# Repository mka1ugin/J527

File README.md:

# J527
## Дополнительный контроллер для подрулевого блока 5K0953569, реализующий работу кнопки ассистентов, круиза и обогрева руля

Руль от Skoda 2021 5E3419093CVKH оборудован обогревом руля, кнопкой включения и выключения подогрева, а также кнопками быстрого вызова ассистентов и установки скорости круиз-контроля. Руль дооснащён LIN-LIN конвертером https://github.com/mka1ugin/LIN_MFSW_Adapter и установлен на VW Passat B6.
Подрулевой блок 5K0953569T доработан путём установки дополнительных шлейфов обогрева руля от блока 5Q1953569B. 
Контроллер выполнен на МК STM32F103C8T6 и реализует следующие функции:
* Управление работой обогрева руля
* Эмуляция нажатия кнопки быстрого вызова ассистентов
* Эмуляция нажатия кнопки задания скорости круиз-контроля

## Контроль обогрева руля

Сигнал нажатия кнопки обогрева руля отслеживается через LIN-шину. Нажатие кнопки включает и выключает обогрев руля. Питание на обогрев подаётся с клеммы 15 и только при включенном зажигании. Кроме того, контроллер отслеживает напряжение питания и работа возможна только при напряжении выше 12.5 В (настраивается в прошивке), т.е. при работающем двигателе. Силовой ключ VN7010A взят из блока 5Q1953569B.
Контроллер оборудован FRAM-памятью FM24CL16, в которую записывается каждое изменение состояния обогрева. Таким образом, если машина была заглушена со включенным обогревом, при следующем запуске двигателя обогрев будет включен автоматически.

## Эмуляция нажатия кнопок

Контроллер управляет двумя герконовыми реле серии EDR3. Их контактные группы включены параллельно штатным кнопкам "SET" круиз-контроля и кнопке быстрого вызова ассистентов. Контакты геркона дублируют состояние соответствующих кнопок на руле.

## Реализация

Контроллер выполнен на односторонней плате размером 50x47.5 мм и соединяется с блоком подрулевых переключателей двумя разъёмами: трёхконтактный - питание 12В и LIN-шина, и пятиконтактный - эмуляция нажатия кнопок. Также контроллер имеет два силовых четырёхконтактных разъёма - вход силового питания и выход на шлейф обогрева.

## Видео работы:
<p align="center">
  <a href="https://youtu.be/Oqg4uzVC5qI">
</p>

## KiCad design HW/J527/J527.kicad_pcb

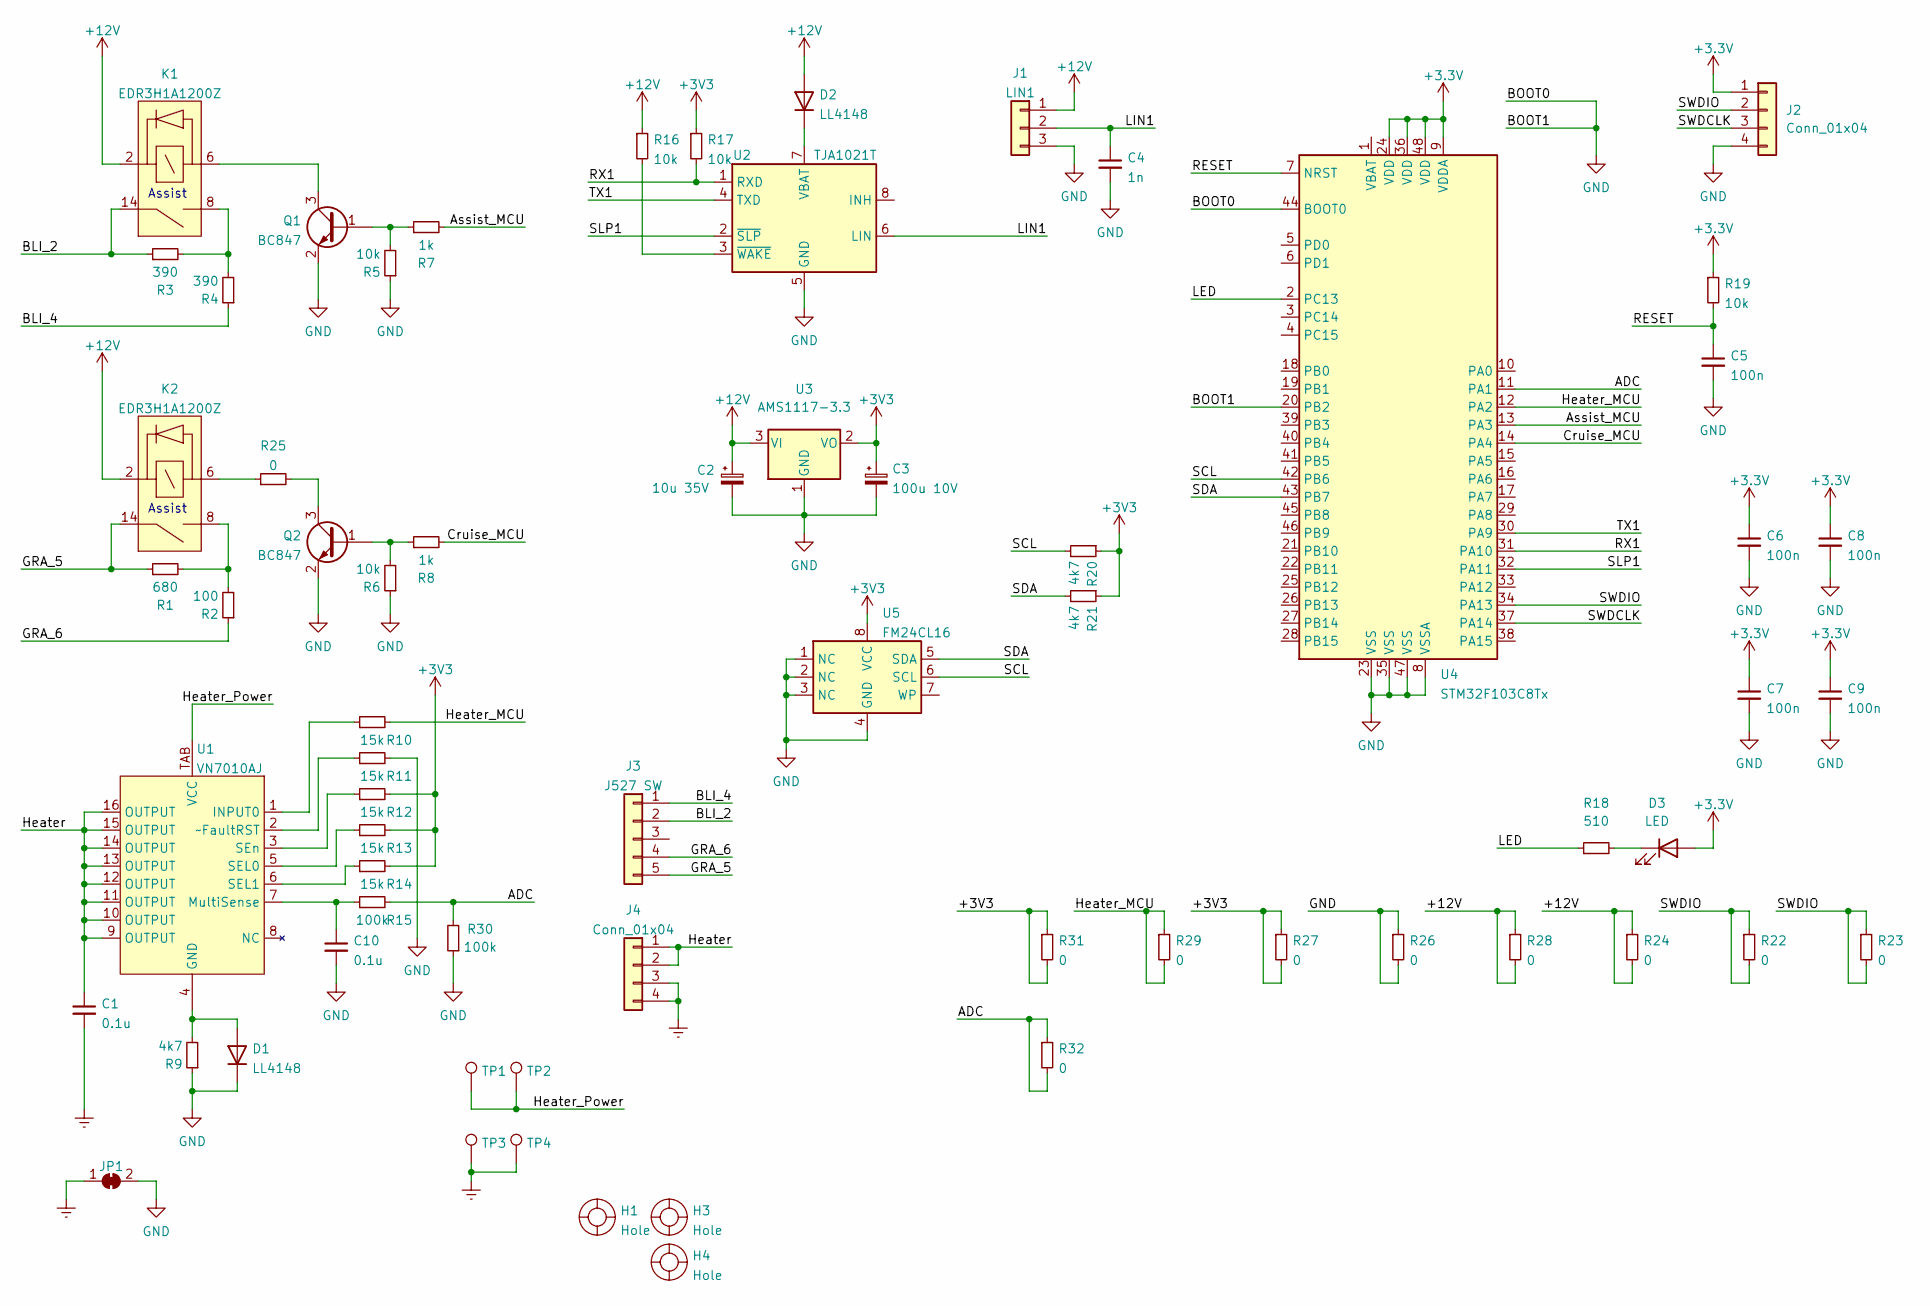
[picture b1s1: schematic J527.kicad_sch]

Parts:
C1, C10: 0.1u; C_0805_2012Metric_Pad1.18x1.45mm_HandSolder
C2: 10u 35V; CP_EIA-7343-31_Kemet-D_Pad2.25x2.55mm_HandSolder
C3: 100u 10V; CP_EIA-7343-31_Kemet-D_Pad2.25x2.55mm_HandSolder
C4: 1n; C_0805_2012Metric_Pad1.18x1.45mm_HandSolder
C5, C6, C7, C8, C9: 100n; C_0805_2012Metric_Pad1.18x1.45mm_HandSolder
D1, D2: LL4148; D_MiniMELF
D3: LED; LED_1206_3216Metric_Pad1.42x1.75mm_HandSolder
H1, H3, H4: Hole; Hole 3 mm
J1: LIN1; B3B-AM
J2: Conn_01x04; SMD_SWD_Connector
J3: J527 SW; B5B-AM
J4: Conn_01x04; B4B-AM
JP1: SolderJumper_2_Bridged; SolderJumper-2_P1.3mm_Bridged_Pad1.0x1.5mm
K1, K2: EDR3H1A1200Z
Q1, Q2: BC847; SOT-23
R1: 680; R_0805_2012Metric_Pad1.20x1.40mm_HandSolder
R2: 100; R_0805_2012Metric_Pad1.20x1.40mm_HandSolder
R3, R4: 390; R_0805_2012Metric_Pad1.20x1.40mm_HandSolder
R5, R6, R16, R17, R19: 10k; R_0805_2012Metric_Pad1.20x1.40mm_HandSolder
R7, R8: 1k; R_0805_2012Metric_Pad1.20x1.40mm_HandSolder
R9, R20, R21: 4k7; R_0805_2012Metric_Pad1.20x1.40mm_HandSolder
R10, R11, R12, R13, R14: 15k; R_0805_2012Metric_Pad1.20x1.40mm_HandSolder
R15, R30: 100k; R_0805_2012Metric_Pad1.20x1.40mm_HandSolder
R18: 510; R_0805_2012Metric_Pad1.20x1.40mm_HandSolder
R22, R23, R24, R25, R26, R27, R28, R29, R31, R32: 0; R_1206_3216Metric_Pad1.30x1.75mm_HandSolder
TP1, TP2: Heat_PW; TestPoint_THTPad_D2.0mm_Drill1.0mm
TP3, TP4: GND; TestPoint_THTPad_D2.0mm_Drill1.0mm
U1: VN7010AJ; PowerSSO-16
U2: TJA1021T; SOIC-8_3.9x4.9mm_P1.27mm
U3: AMS1117-3.3; SOT-223-3_TabPin2
U4: STM32F103C8Tx; LQFP-48_7x7mm_P0.5mm
U5: FM24CL16; SO-8_3.9x4.9mm_P1.27mm

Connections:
+12V: C2.1, D2.2 (A), J1.1, K1.2, K2.2, R16.1, R24.1, R24.2, R28.1, R28.2, U3.3 (VI)
/ADC: R15.2, R30.2, R32.1, R32.2, U4.11 (PA1)
/Assist_MCU: R7.2, U4.13 (PA3)
/BLI_2: J3.2, K1.14, R3.1
/BLI_4: J3.1, R4.1
/Cruise_MCU: R8.2, U4.14 (PA4)
/GRA_5: J3.5, K2.14, R1.1
/GRA_6: J3.4, R2.1
/Heater: C1.1, J4.1, J4.2, U1.9 (OUTPUT), U1.10 (OUTPUT), U1.11 (OUTPUT), U1.12 (OUTPUT), U1.13 (OUTPUT), U1.14 (OUTPUT), U1.15 (OUTPUT), U1.16 (OUTPUT)
/Heater_MCU: R10.2, R29.1, R29.2, U4.12 (PA2)
/Heater_Power: TP1.1, TP2.1, U1.TAB (VCC)
/LED: R18.1, U4.2 (PC13)
/LIN1: C4.1, J1.2, U2.6 (LIN)
/RESET: C5.1, R19.2, U4.7 (NRST)
/RX1: R17.2, U2.1 (RXD), U4.31 (PA10)
/SCL: R20.2, U4.42 (PB6), U5.6 (SCL)
/SDA: R21.2, U4.43 (PB7), U5.5 (SDA)
/SLP1: U2.2 (~SLP), U4.32 (PA11)
/SWDCLK: J2.3, U4.37 (PA14)
/SWDIO: J2.2, R22.1, R22.2, R23.1, R23.2, U4.34 (PA13)
/TX1: U2.4 (TXD), U4.30 (PA9)
Earth: C1.2, J4.3, J4.4, JP1.1 (A), TP3.1, TP4.1
GND: C2.2, C3.2, C4.2, C5.2, C6.2, C7.2, C8.2, C9.2, C10.2, D1.1 (K), J1.3, J2.4, JP1.2 (B), Q1.2 (E), Q2.2 (E), R5.1, R6.1, R9.1, R11.2, R26.1, R26.2, R30.1, U2.5 (GND), U3.1 (GND), U4.8 (VSSA), U4.20 (PB2), U4.23 (VSS), U4.35 (VSS), U4.44 (BOOT0), U4.47 (VSS), U5.1 (NC), U5.2 (NC), U5.3 (NC), U5.4 (GND)
unnamed: C10.1, R15.1, U1.7 (MultiSense)
unnamed: D1.2 (A), R9.2, U1.4 (GND)
unnamed: D2.1 (K), U2.7 (VBAT)
unnamed: D3.1 (K), R18.2
unnamed: K1.6, Q1.3 (C)
unnamed: K1.8, R3.2, R4.2
unnamed: K2.6, R25.1
unnamed: K2.8, R1.2, R2.2
unnamed: Q1.1 (B), R5.2, R7.1
unnamed: Q2.1 (B), R6.2, R8.1
unnamed: Q2.3 (C), R25.2
unnamed: R10.1, U1.1 (INPUT0)
unnamed: R11.1, U1.2 (~FaultRST)
unnamed: R12.1, U1.3 (SEn)
unnamed: R13.1, U1.5 (SEL0)
unnamed: R14.1, U1.6 (SEL1)
unnamed: R16.2, U2.3 (~WAKE)

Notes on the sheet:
Assist

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
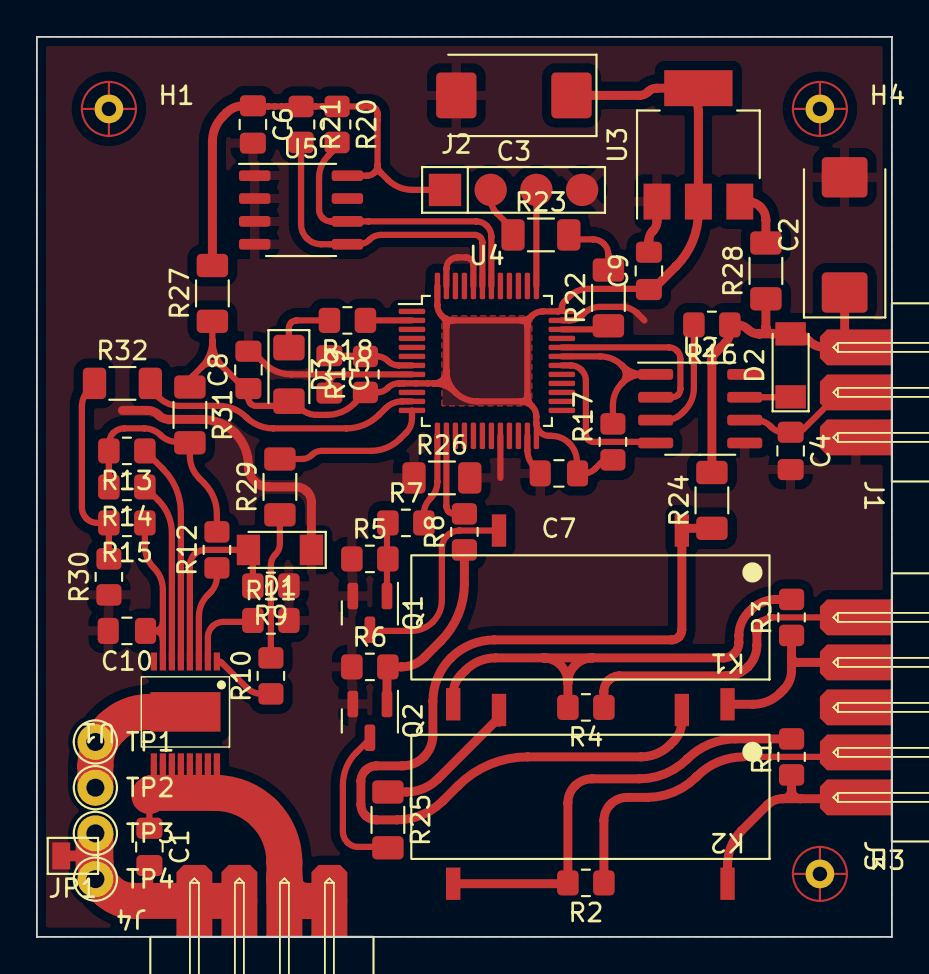
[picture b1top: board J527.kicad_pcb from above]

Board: 2 copper layers, 47.5 x 50.0 mm, 66 parts (0 on the bottom side), 41 nets.

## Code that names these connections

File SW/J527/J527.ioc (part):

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Mcu.Name=STM32F103C(8-B)Tx
Mcu.Package=LQFP48
Mcu.UserName=STM32F103C8Tx
PA1.GPIOParameters=GPIO_Label
PA1.GPIO_Label=Voltage_ADC
PA1.Signal=ADCx_IN1
PA10.Mode=LIN
PA10.Signal=USART1_RX
PA11.GPIOParameters=GPIO_Label
PA11.GPIO_Label=USART1_SLP
PA11.Signal=GPIO_Output
PA13.Signal=SYS_JTMS-SWDIO
PA2.GPIOParameters=GPIO_Label
PA2.GPIO_Label=Heater
PA2.Signal=GPIO_Output
PA3.GPIOParameters=GPIO_Label
PA3.GPIO_Label=Assist
PA3.Signal=GPIO_Output
PA4.GPIOParameters=GPIO_Label
PA4.GPIO_Label=Cruise
PA4.Signal=GPIO_Output
PA9.Mode=LIN
PA9.Signal=USART1_TX
PB6.Mode=I2C
PB6.Signal=I2C1_SCL
PB7.Mode=I2C
PB7.Signal=I2C1_SDA
PC13-TAMPER-RTC.GPIOParameters=GPIO_Label
PC13-TAMPER-RTC.GPIO_Label=LED
PC13-TAMPER-RTC.Signal=GPIO_Output
board=custom
